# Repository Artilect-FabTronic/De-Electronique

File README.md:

# Projet de dé électronique

L'ambition de ce projet, est de vous permettre de vous initier à la conception d'une carte électronique à travers un exemple simple, que vous concevrez vous même.
Une fois que vous s'aurez dessiner et réaliser un premier circuit imprimer (PCB), vous pourrez réaliser vos propres montages électroniques.

## Description

On se propose de réaliser le dé électronique d'Heliox, qui lorsqu'on le secoue, tire un numéro de 1 à 6 de manière aléatoire.

L'objectif est d'avoir un système minimaliste afin de pouvoir le faire fonctionner à partir d'une pile bouton de 3V.

Nous utiliserons donc un microcontrôleur ATtiny85 du fabricant Microchip, compatible avec les cartes Arduino ([ATtiny microcontroller comparison chart](https://en.wikipedia.org/wiki/ATtiny_microcontroller_comparison_chart)).

Voici deux sources du projet, parmi d'autres que vous retrouverez sur Internet.

1. <http://carrefour-numerique.cite-sciences.fr/wiki/doku.php?id=projets:de_electronique>

2. Le tutoriel d'Heliox est articulé en 4 épisodes :
    1. 📺 [Fabrication d'un circuit imprimé avec transfert de toner](https://youtu.be/8joLK039fjk)
    2. 📺 [Explication rapide du circuit imprimé et comment placer les composants dessus](https://youtu.be/6BOH1eVT2Hk)
    3. 📺 [Programmation du microcontrôleur ATtiny85 pour faire fonctionner le dé](https://youtu.be/S-oBujsoe-Q), [Code source HelioxLab](https://github.com/HelioxLab/electronicdice)
    4. 📺 [Création et modélisation de l'objet 3D final](https://youtu.be/o8AYCznNaCQ)

<!-- Routage du PCB réalisé par Heliox avec le logiciel  <https://fritzing.org/download/> -->

## Evolution possible du projet

- Projet initial à partir du tutoriel d'Heliox et des composants traversants
- Même projet mais avec une carte électronique supportant des composants CMS
- Autre version avec l'utilisation de [registre à décalage](https://fr.wikipedia.org/wiki/Registre_%C3%A0_d%C3%A9calage) pour le pilotage des LED
- [Projet plus ambitieux avec des LED sur toutes les faces](https://www.youtube.com/watch?v=6NPTslF68Q0&ab_channel=maker.moekoe)

## Les outils logiciels utilisés

- CAO éléctronique KiCad en version 5.99 "[Nightly Development Builds](https://www.kicad.org/download/windows/)", est téléchargeable depuis la page du serveur, aller tout en bas pour trouver la dernière date de compilation :
<https://kicad-downloads.s3.cern.ch/index.html?prefix=windows/nightly/>
- CAO mécanique [FreeCAD](https://www.freecadweb.org/?lang=fr)
- [Arduino IDE 1.8.15](https://www.arduino.cc/en/software)
- [Visual Studio Code](https://code.visualstudio.com/)

## Le matériel du projet dé électronique (BOM)

- Matériaux PLA pour l'imprimante 3D, à partir des [fichiers STL fournis par HELIOX](https://www.thingiverse.com/thing:2798081)
- Un fer à souder pour assembler les composants sur le circuit imprimé (PCB), ainsi qu'un petit outillage, comme un multimètre, des pinces, etc...
- [Interrupteur à bascule 3 broches 1P2T, poignée haute 4 mm, SS12F15](https://fr.aliexpress.com/item/32765155281.html)
- [Piles bouton au Lithium 3V, CR2032](https://fr.aliexpress.com/item/1005001314447472.html)
- [ATtiny85](https://www.microchip.com/wwwproducts/en/ATtiny85), [Microcontrôleur MCU 8BIT 20MHZ, 8 broches DIP-8 ATTINY85](https://fr.aliexpress.com/item/32952262601.html), [ATTINY85V-10PU](https://octopart.com/attiny85v-10pu-microchip-77762335), [Farnell 1455165](https://fr.farnell.com/microchip/attiny85v-10pu/mcu-8bit-attiny-10mhz-dip-8/dp/1455165) (l'option V permet de descendre la tension d'alimentation jusqu'à 1V8)
- Interrupteur à bille (mouvement et inclinaison) : [Capteur de vibrations en métal, Boule d'inclinaison secouant commutateur, SW-520D SW520D](https://www.aliexpress.com/item/100PCS-SW-520D-SW520D-Vibration-Sensor-Metal-Ball-Tilt-Shaking-Switch/4000680935322.html)
- [Kit de LED, taille 5 mm, 2V ou 3 V, ensemble d'ampoules couleurs chaudes, blanc, rouge, bleu, vert, orange, jaune](https://fr.aliexpress.com/item/1936218827.html)
- [Assortiment de condensateurs électrolytiques, 125 Pieces 1uF 2200uF 25 Valeurs](https://www.amazon.fr/gp/product/B00JZETYIG/ref=ppx_yo_dt_b_asin_title_o01_s00)
- [Boîtier/Socket support DIP 8 broches, 0.3 inch / 7.62mm](https://www.amazon.fr/gp/product/B016S6ZQQM/ref=ppx_yo_dt_b_asin_title_o00_s00)
- [Kit résistance à fil métallique, 600 pcs/lot, 30 valeurs* 20 pcs de 10 ohms ~ 1 M ohm, 1 %, 1/4 W](https://fr.aliexpress.com/item/1005001774876666.html)
- [Support de piles, CR2032, pour piles bouton 3V](https://fr.aliexpress.com/item/32845557622.html),  modèle 3D : [20mm THT Coin Cell Holder](https://grabcad.com/library/20mm-tht-coin-cell-holder-1)

---

## Schématique

"arduino attiny85 pinout" depuis la page : https://learn.sparkfun.com/tutorials/tiny-avr-programmer-hookup-guide/attiny85-use-hints

Brochage (Pinout en Anglais) de l'ATtiny85 :

[Programmation de l’ATtiny85](http://makerspace56.org/transformer-une-arduino-uno-en-programmateur-isp-dattiny-par-exemple/)

Afin de pouvoir programmer l'ATtiny85, nous utiliserons un connecteur dit **_ISP_** ou **_ICSP_** pour In-circuit Serial Programmer, de 2x3 broches, voir [Arduino as ISP and Arduino Bootloaders](https://www.arduino.cc/en/pmwiki.php?n=Tutorial/ArduinoISP).

Nous pouvons nous inspirer du schéma d'implantation du connecteur de programmation ICSP à partir du schéma de la [carte Arduino Nano](https://store.arduino.cc/arduino-nano).

Et pour la programmation, suivre les instruction ici : [Programming ATtiny85 with Arduino Uno](https://create.arduino.cc/projecthub/arjun/programming-attiny85-with-arduino-uno-afb829)

Si vous avez tous suivi, vous aurez vu que par défaut, l'environnement Arduino IDE ne prend pas en charge les microcontrôleurs ATtiny85. Nous devons donc ajouter les cartes ATtiny à l'IDE Arduino.

Pour cela, ouvrez le menu "Fichier -> Préférences" et dans les URL du gestionnaire de cartes supplémentaires, ajoutez cette URL :

`https://raw.githubusercontent.com/damellis/attiny/ide-1.6.x-boards-manager/package_damellis_attiny_index.json`

Puis ajouter le support pour les [ATtiny](https://github.com/damellis/attiny) depuis le gestionnaire de carte.

Une fois cela effectué, vous pourrez choisir le type de carte ATtiny25/45/85, préciser bien le modèle du "processeur" ATtiny85 et le choix de l'horloge interne à 8 MHz.

TODO: passer à 1 MHz et voir la différence de consommation...

## Carte électronique

### Programmation de l'ATtiny85 depuis une carte Arduino Uno

Une fois le programme compilé sous l'IDE Arduino (version 1.8.16 sous Windows 10, avec les paramètres de carte : "ATtiny25/45/85, ATtiny85, Internal 8 MHz"), il est important pour la programmation de votre ATtiny85 cible de bien configurer le programmer externe, afin de pouvoir effectuer la programmation.

---

### Description du fonctionnement

Nous allons étudier ensemble le montage électronique ;-)

Le microcontrôleur ATtiny85 dispose de 8 broches, dont 2 sont réservées pour son alimentation électrique.

Nous devons donc sélectionner les broches numériques d'entrées/sorties (E/S) permettant le bon fonctionnement de notre projet.

Tout d'abord, nous aurons besoin d'une entrée pour le capteur de mouvement à bille.
Il faut alors ce pencher sur les fonctions des broches du microcontrôleur afin de pouvoir décider quelle broche nous sera utile afin de pouvoir détecter cet évènement.

Mettre les LED sous la forme du dé avec une numérotation Ligne/Colonne (L/C) :

|   L/C  |  C1  |  C2  |  C3  |
|:------:|:----:|:----:|:----:|
| **L1** | L1C1 | L1C2 | L1C3 |
| **L2** | L2C1 | L2C2 | L2C3 |
| **L3** | L3C1 | L3C2 | L3C3 |

- Chiffre 1 : (L2C2)
- Chiffre 2 : (L3C1 + L1C3)
- Chiffre 3 : (L3C1 + L1C3) + (L2C2)
- Chiffre 4 : (L3C1 + L1C3) + (L1C1 + L3C3)
- Chiffre 5 : (L3C1 + L1C3) + (L1C1 + L3C3) + (L2C2)
- Chiffre 6 : (L3C1 + L1C3) + (L1C1 + L3C3) + (L2C1 + L2C3)

En regroupant les LED entre parenthèse, nous voyant que nous devons piloter séparément les groupes suivant, si l'on veux pouvoir afficher tous les chiffres :

- 1 broche en sortie pour commander la LED L2C2, nous la nommerons CMD_L2C2
- 1 broche en sortie pour commander les LED L3C1 et L1C3, nous la nommerons CMD_L3C1L1C3
- 1 broche en sortie pour commander les LED L1C1 et L3C3, nous la nommerons CMD_L1C1L3C3
- 1 broche en sortie pour commander les LED L2C1 et L2C3, nous la nommerons CMD_L2C1C3

Soit un total de 4 broches en sorties pour la commande des LED du projet :

Consommation en veille = 373 uA
Consommation au repos = 800 uA
Consommation avec 1 LED = 2.62 mA
Consommation avec 4 LED = 8.13 mA

---

## Internet ⚀, ⚁, ⚂, ⚃, ⚄, ⚅

- [Dé — Wikipédia](https://fr.wikipedia.org/wiki/D%C3%A9)
- [Lancez un dé virtuel!](https://de.virtuworld.net/)
- [Patrons de dés à jouer](https://www.fiche-maternelle.com/fabriquer-son-des-a-jouer.html)
- [Fabriquer soit même un Dé électronique sans Arduino](https://www.youtube.com/watch?v=spbdDq6kvxw&ab_channel=ElectroMic)
- [dé électronique qui se déclenche par passage de la main au dessus d'une photorésistance](https://sciences-du-numerique.fr/projet-arduino-pour-la-specialite-isn/de-electronique/41)

---

## License

[Open Hardware](https://fr.wikipedia.org/wiki/Mat%C3%A9riel_libre)

[MIT License](https://opensource.org/licenses/MIT)

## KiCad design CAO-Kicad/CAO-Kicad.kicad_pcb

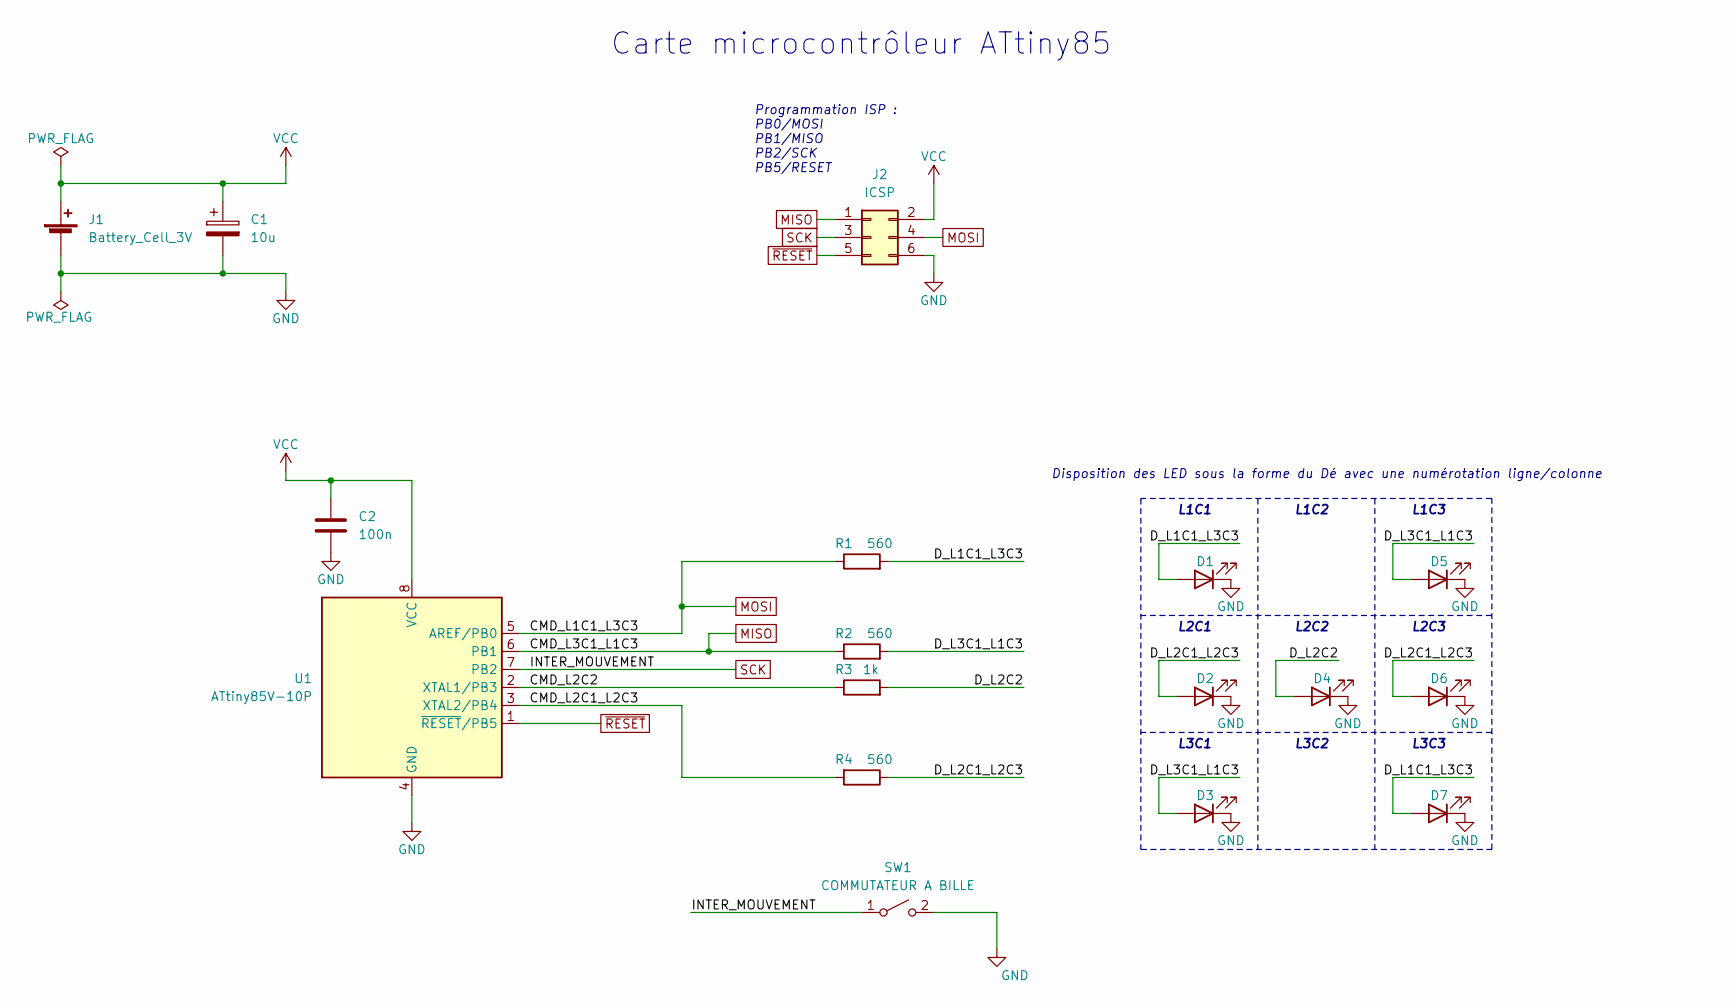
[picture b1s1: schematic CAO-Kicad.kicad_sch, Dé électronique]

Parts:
C1: 10u; CP_Radial_D5.0mm_P2.50mm
C2: 100n; C_Rect_L7.2mm_W3.0mm_P5.00mm_FKS2_FKP2_MKS2_MKP2
D1, D2, D3, D4, D5, D6, D7: LED; LED_D5.0mm_Clear
J1: Battery_Cell_3V; PinHeader_1x02_P2.54mm_Vertical
J2: ICSP; PinHeader_2x03_P2.54mm_Vertical
R1, R2, R4: 560; R_Axial_DIN0207_L6.3mm_D2.5mm_P10.16mm_Horizontal
R3: 1k; R_Axial_DIN0207_L6.3mm_D2.5mm_P10.16mm_Horizontal
SW1: COMMUTATEUR A BILLE; CP_Radial_D4.0mm_P2.00mm
U1: ATtiny85V-10P; DIP-8_W7.62mm_LongPads

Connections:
/CMD_L2C1_L2C3: R4.2, U1.3 (XTAL2/PB4)
/CMD_L2C2: R3.1, U1.2 (XTAL1/PB3)
/D_L1C1_L3C3: D1.2 (A), D7.2 (A), R1.2
/D_L2C1_L2C3: D2.2 (A), D6.2 (A), R4.1
/D_L2C2: D4.2 (A), R3.2
/D_L3C1_L1C3: D3.2 (A), D5.2 (A), R2.2
GND: C1.2, C2.2, D1.1 (K), D2.1 (K), D3.1 (K), D4.1 (K), D5.1 (K), D6.1 (K), D7.1 (K), J1.2 (-), J2.6, SW1.2 (B), U1.4 (GND)
MISO: J2.1, R2.1, U1.6 (PB1)
MOSI: J2.4, R1.1, U1.5 (AREF/PB0)
SCK: J2.3, SW1.1 (A), U1.7 (PB2)
VCC: C1.1, C2.1, J1.1 (+), J2.2, U1.8 (VCC)
~RESET: J2.5, U1.1 (~RESET/PB5)

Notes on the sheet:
Carte microcontrôleur ATtiny85
Programmation ISP : PB0/MOSI PB1/MISO PB2/SCK PB5/RESET
Disposition des LED sous la forme du Dé avec une numérotation ligne/colonne
L1C1
L2C1
L3C1
L1C2
L2C2
L3C2
L1C3
L2C3
L3C3

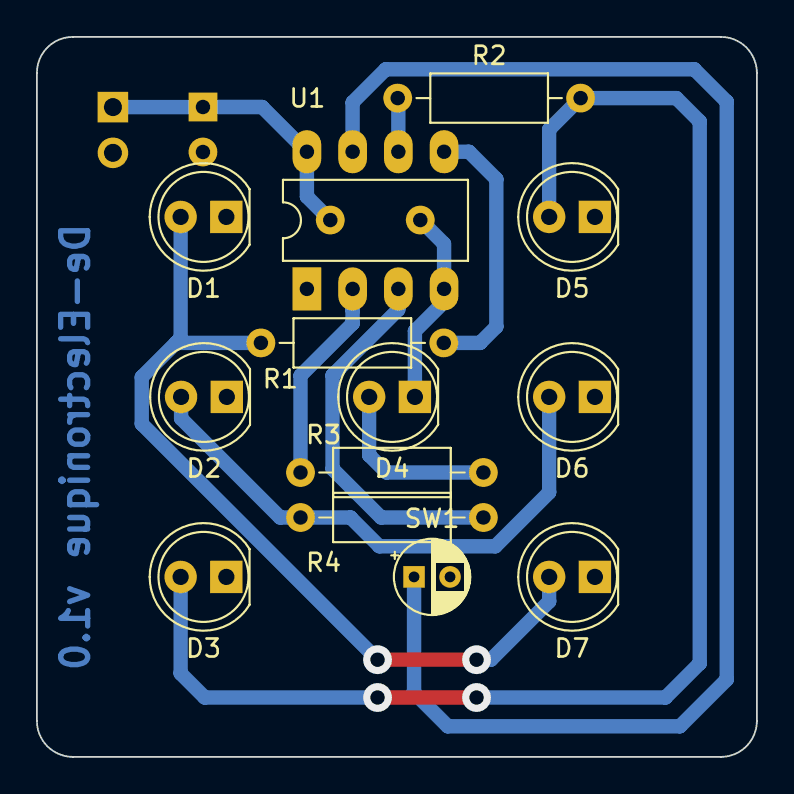
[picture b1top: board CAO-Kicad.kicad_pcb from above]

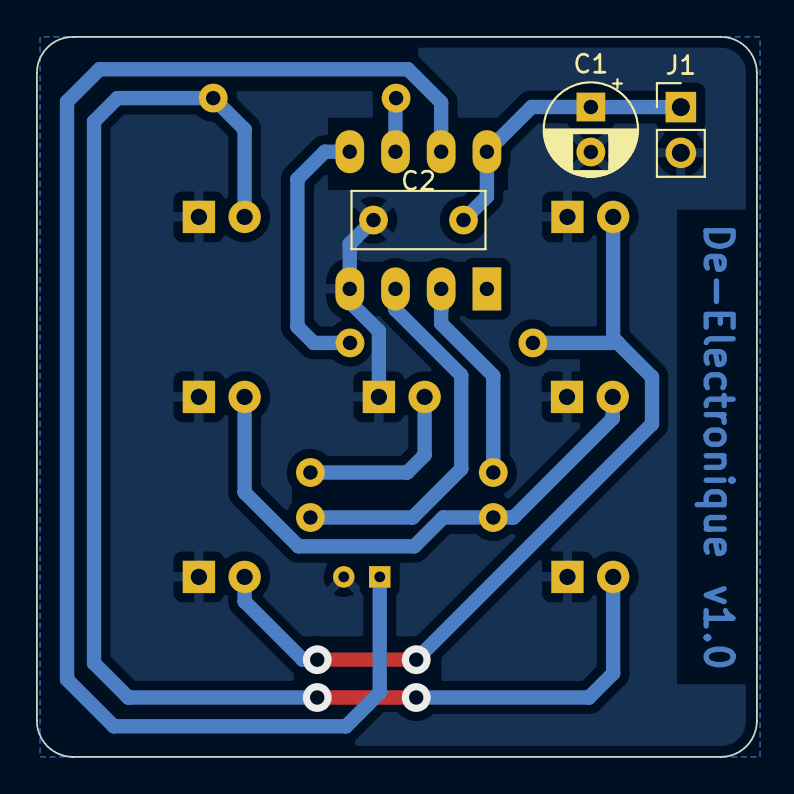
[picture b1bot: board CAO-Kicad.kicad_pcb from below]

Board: 2 copper layers, 40.0 x 40.0 mm, 16 parts (3 on the bottom side), 11 nets.

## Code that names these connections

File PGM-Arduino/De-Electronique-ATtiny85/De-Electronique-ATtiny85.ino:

/**
   Projet du dé électronique - FabTronic 2021
   Source : 
   
   ATtiny85 (8MHz)

   Libraries used are the properties of the respective authors.

   Sleep mode use about 70 µA (0.07 mA)

   Battery life in sleep mode, assuming 10 wake-ups pr.hour:
   ----------------------------------------------------------
   2 x AA at 2500mAh      =
   1 x 3.7v Saft LS14500  =
   1 x 550mAh coin cell   =
   1 x 240mAh coin cell   =
   ----------------------------------------------------------
   Battery Life Calculator <http://oregonembedded.com/batterycalc.htm>

   Reference > Language > Functions > Random numbers > Random
   https://www.arduino.cc/reference/en/language/functions/random-numbers/random/

*/


// ATMEL ATTINY 25/45/85 / ARDUINO
//
//                  +--\/--+
// Ain0 (D 5) PB5  1|      |8  Vcc
// Ain3 (D 3) PB3  2|      |7  PB2 (D 2) Ain1 / INT0
// Ain2 (D 4) PB4  3|      |6  PB1 (D 1) pwm1
//            GND  4|      |5  PB0 (D 0) pwm0
//                  +------+

#include <avr/io.h>
#include <avr/interrupt.h>
//#define F_CPU 8000000ul
#include <util/delay.h>
#include <avr/sleep.h>

#define adc_disable() (ADCSRA &= ~(1<<ADEN)) // disable ADC (before power-off)

//#warning "F CPU = "
//#warning F_CPU

/*
Correspondance des E/S avec <http://carrefour-numerique.cite-sciences.fr/wiki/doku.php?id=projets:de_electronique>
PB0 = CMD_L1C1L3C3 // Leds 1 et 6
PB1 = CMD_L3C1L1C3 // Leds 2 et 5
PB2 = SW1, COMMUTATEUR A BILLE
PB3 = CMD_L2C2 // Led 7
PB4 = CMD_L2C1C3 // Leds 3 et 4
*/
#define LEDUNSIX       0     // Leds 1 et 6 sur PB1
#define LEDTROISQUATRE 4     // Leds 3 et 4 sur PB5
#define LEDDEUXCINQ    1     // Leds 2 et 5 sur PB4
#define LEDSEPT        3     // Leds 7 sur PB3

#define UNESECONDE     100   // 1 seconde égal à 1000 ms --> TODO: Déterminer la Fq de travail et la bonne valeur

volatile uint8_t roll = 0, initSeed = 0, seed = 0;

ISR(INT0_vect) {
  MCUCR &= ~(1 << SE); // Idle of sleep mode -> disable
  roll = 1;
  if (initSeed == 0) {
    randomSeed(seed);
    initSeed = 1;
  }
}

void action() {
  uint8_t tirage = 0;
  uint8_t newTirage = 0;

  //  for (uint8_t i = 0; i < random(10, 21); i++) {
  for (uint8_t i = 0; i < random(3, 11); i++) {
    do {
      newTirage = random(1, 7);
    } while (tirage == newTirage);
    tirage = newTirage;

    onEteind();
    afficheTirage(tirage); // on affiche le tirage
    _delay_ms(UNESECONDE / 4);
  }

  // Phase de tirage réel
  onEteind();
  do {
    newTirage = random(1, 7);
  } while (tirage == newTirage);

  afficheTirage(newTirage);
  _delay_ms(UNESECONDE * 5);  // Tirage final, on fait une pause de 5 secondes
  onEteind();
  roll = 0;
}

void init_ISR() { // INITIALISATION des routines d'initialisation
  PORTB |= 1 << PB2;   // configuration du bit 0 du port B avec résistance de PULL UP (PB2)
  MCUCR |= 1 << ISC01; // Falling EDGE INT0 (PB2)
  GIMSK |= 1 << INT0;  // Activate the INT0
  sei();               // Active General Interrupt
}

void init_GPIO() {
  // On configure les PINs en sortie pour les LEDs
  DDRB |= (1 << LEDUNSIX) | (1 << LEDTROISQUATRE) | (1 << LEDDEUXCINQ) | (1 << LEDSEPT);
}

void onEteind() {
  PORTB &= ~((1 << LEDUNSIX) | (1 << LEDTROISQUATRE) | (1 << LEDDEUXCINQ) | (1 << LEDSEPT));
  _delay_ms(UNESECONDE / 5);
}

void afficheTirage(uint8_t tirage) {
  PORTB &= ~((1 << LEDUNSIX) | (1 << LEDTROISQUATRE) | (1 << LEDDEUXCINQ) | (1 << LEDSEPT));
  switch (tirage) {
    case 1:
      PORTB |= (1 << LEDSEPT);
      break;
    case 2:
      PORTB |= (1 << LEDUNSIX);
      break;
    case 3:
      PORTB |= (1 << LEDUNSIX) | (1 << LEDSEPT);
      break;
    case 4:
      PORTB |= (1 << LEDUNSIX) | (1 << LEDDEUXCINQ);
      break;
    case 5:
      PORTB |= (1 << LEDUNSIX) | (1 << LEDDEUXCINQ) | (1 << LEDSEPT);
      break;
    case 6:
      PORTB |= (1 << LEDUNSIX) | (1 << LEDDEUXCINQ) | (1 << LEDTROISQUATRE);
      break;

    default:
      // if nothing else matches, do the default
      // default is optional
      break;
  }
}

int main() {
  init_GPIO();
  init_ISR();
  adc_disable();

  while (1) {
    if (initSeed == 0) {
      seed++;
    }

    if (roll == 1) {
      action();
      MCUCR |= (1 << SE); // Idle Mode of sleep mode
      sleep_mode();
    }
  }

  return 0;
}

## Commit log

2021-07-26 ajout projet Kicad
2021-07-29 Ajout du conn ICSP et du contour de carte 100x100mm
2021-08-10 Ajout de la serigraphie et recherche composants
2021-08-23 Ajout des docs et images
2021-08-23 Importation des composants vers le circuit imprimé
2021-09-20 MAJ pour la realiser un PCB de 40x40 mm
2021-09-20 Routage de la carte electronique
2021-10-03 MAJ nommenclature
2021-10-07 mod the prog file. Disabled the ADC
2021-10-16 Mise à jour du fichier README
2021-10-17 add chris file
